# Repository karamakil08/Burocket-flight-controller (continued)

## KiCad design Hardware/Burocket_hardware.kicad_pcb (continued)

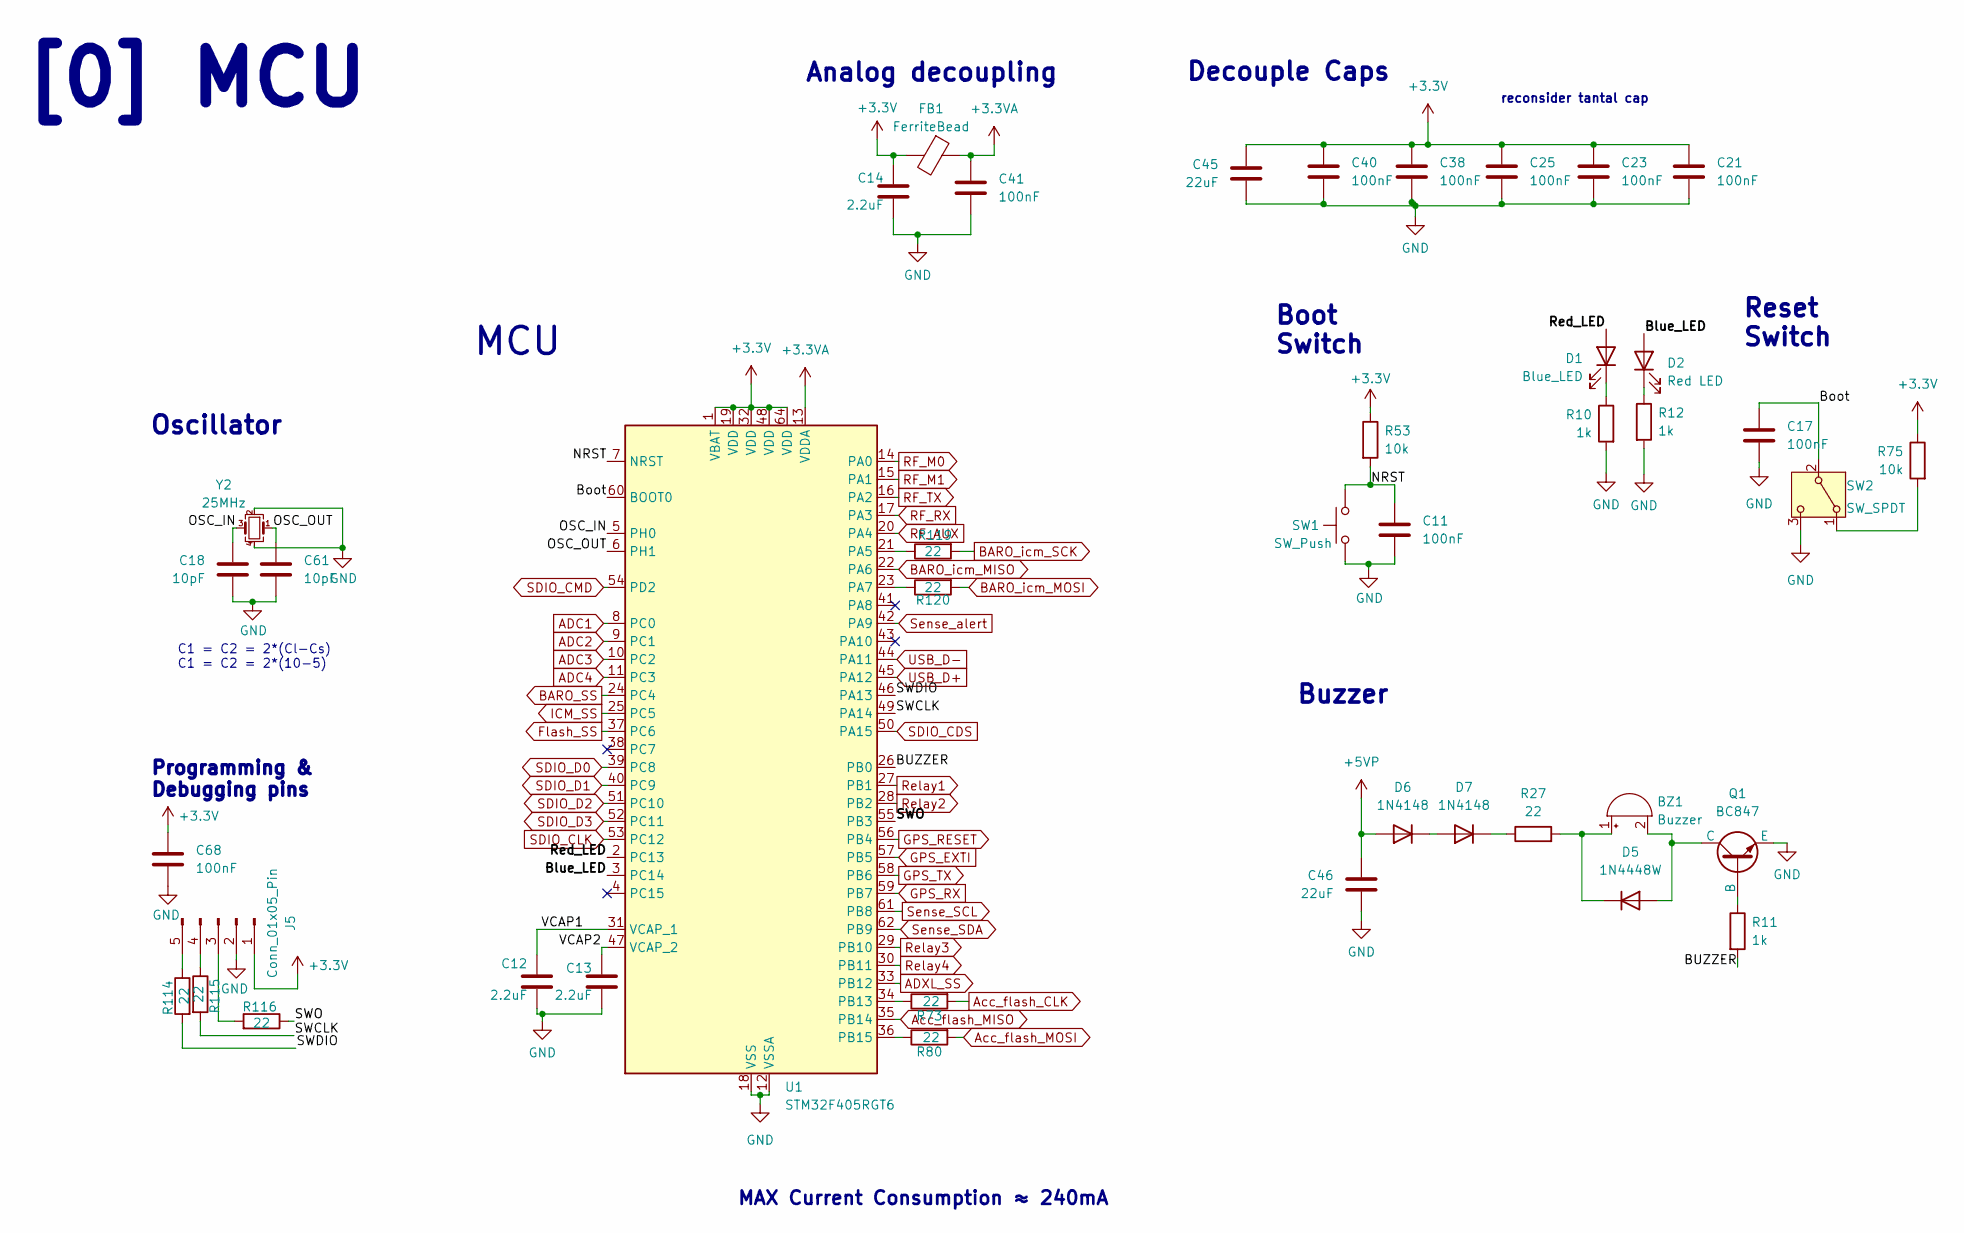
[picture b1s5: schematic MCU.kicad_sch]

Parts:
BZ1: Buzzer; Buzzer_typeshit; Part Number L-KLS3-SMT-3020-3V
C11, C17, C21, C23, C25, C38, C40, C41, C68: 100nF; C_0603_1608Metric; Part Number CL10B104KO8WPNC
C12, C13, C14: 2.2uF; C_0603_1608Metric; Part Number CL10B225KP8NNNC
C18, C61: 10pF; C_0603_1608Metric; Part Number CL10C100JB81PNC
C45, C46: 22uF; C_0805_2012Metric; Part Number CL21A226KOQNNNE
D1: Blue_LED; C_0603_1608Metric; Part Number HL-PST-1608H203BC
D2: Red LED; C_0603_1608Metric; Part Number 27-21/R6C-AP1Q2B/3C
D5: 1N4448W; Nexperia_CFP3_SOD-123W; Part Number 1N4448W_R1_00001
D6, D7: 1N4148; D_SOD-523; Part Number 1N4148WT
FB1: FerriteBead; R_0603_1608Metric; Part Number BLM18HE601SN1D
J5: Conn_01x05_Pin; PinHeader_1x05_P2.54mm_Vertical
Q1: BC847; SOT-323_SC-70; Part Number BC817-40W_R1_00001
R10, R11, R12: 1k; R_0603_1608Metric; Part Number CRCW06031K00JNTABC
R27: 22; R_0603_1608Metric; Part Number ERJPA3J220V
R53, R75: 10k; R_0603_1608Metric; Part Number CRT03J7E1002
R73, R80, R114, R115, R116, R119, R120: 22; R_0603_1608Metric; Part Number CQ03SAJ0220T5E
SW1: SW_Push; SW_SPST_PTS810; Part Number PTS815SJK250SMTRLFS
SW2: SW_SPDT; SW_SPDT_CK_JS102011SAQN; Part Number L-KLS7-MSK-12C03
U1: STM32F405RGT6; LQFP-64_10x10mm_P0.5mm
Y2: 25MHz; Crystal_SMD_2520-4Pin_2.5x2.0mm; Part Number ECS-250-10-36Q-ES-TR

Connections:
+3.3V: C14.1, C21.1, C23.1, C25.1, C38.1, C40.1, C45.1, C68.1, FB1.2, J5.1, R53.1, R75.1, U1.1 (VBAT), U1.19 (VDD), U1.32 (VDD), U1.48 (VDD), U1.64 (VDD); also elsewhere on the board
+3.3VA: C41.1, FB1.1, U1.13 (VDDA)
+5VP: C46.1, D6.2 (A); also elsewhere on the board
/MCU/BUZZER: R11.2, U1.26 (PB0)
/MCU/Blue_LED: D2.2 (A), U1.3 (PC14)
/MCU/Boot: C17.1, SW2.2 (B), U1.60 (BOOT0)
/MCU/NRST: C11.1, R53.2, SW1.2, U1.7 (NRST)
/MCU/OSC_IN: C18.1, U1.5 (PH0), Y2.3
/MCU/OSC_OUT: C61.1, U1.6 (PH1), Y2.1
/MCU/Red_LED: D1.2 (A), U1.2 (PC13)
/MCU/SWCLK: R115.2, U1.49 (PA14)
/MCU/SWDIO: R114.2, U1.46 (PA13)
/MCU/SWO: R116.1, U1.55 (PB3)
/MCU/VCAP1: C12.1, U1.31 (VCAP_1)
/MCU/VCAP2: C13.1, U1.47 (VCAP_2)
ADC1: U1.8 (PC0); also elsewhere on the board
ADC2: U1.9 (PC1); also elsewhere on the board
ADC3: U1.10 (PC2); also elsewhere on the board
ADC4: U1.11 (PC3); also elsewhere on the board
ADXL_SS: U1.33 (PB12); also elsewhere on the board
Acc_flash_CLK: R73.2; also elsewhere on the board
Acc_flash_MOSI: R80.2; also elsewhere on the board
BARO_SS: U1.24 (PC4); also elsewhere on the board
BARO_icm_MOSI: R120.2; also elsewhere on the board
Flash_SS: U1.37 (PC6); also elsewhere on the board
GND: C11.2, C12.2, C13.2, C14.2, C17.2, C18.2, C21.2, C23.2, C25.2, C38.2, C40.2, C41.2, C45.2, C46.2, C61.2, C68.2, J5.2, Q1.3 (E), R10.2, R12.2, SW1.1, SW2.3 (C), U1.12 (VSSA), U1.18 (VSS), U1.63 (VSS), Y2.2, Y2.4; also elsewhere on the board
GPS_EXTI: U1.57 (PB5); also elsewhere on the board
GPS_RESET: U1.56 (PB4); also elsewhere on the board
GPS_RX: U1.59 (PB7); also elsewhere on the board
GPS_TX: U1.58 (PB6); also elsewhere on the board
unnamed: BZ1.1 (+), D5.1 (K), R27.2
unnamed: BZ1.2 (-), D5.2 (A), Q1.1 (C)
unnamed: D1.1 (K), R10.1
unnamed: D2.1 (K), R12.1
unnamed: D6.1 (K), D7.2 (A)
unnamed: D7.1 (K), R27.1
unnamed: J5.3, R116.2
unnamed: J5.4, R115.1
unnamed: J5.5, R114.1
unnamed: Q1.2 (B), R11.1
unnamed: R75.2, SW2.1 (A)
unnamed: R119.1, U1.21 (PA5)
unnamed: R120.1, U1.23 (PA7)
unnamed: R73.1, U1.34 (PB13)
unnamed: R80.1, U1.36 (PB15)
RF_AUX: U1.20 (PA4); also elsewhere on the board
RF_M0: U1.14 (PA0); also elsewhere on the board
RF_M1: U1.15 (PA1); also elsewhere on the board
RF_RX: U1.17 (PA3); also elsewhere on the board
RF_TX: U1.16 (PA2); also elsewhere on the board
Relay1: U1.27 (PB1); also elsewhere on the board
Relay2: U1.28 (PB2); also elsewhere on the board
Relay3: U1.29 (PB10); also elsewhere on the board
Relay4: U1.30 (PB11); also elsewhere on the board
SDIO_CDS: U1.50 (PA15); also elsewhere on the board
SDIO_CLK: U1.53 (PC12); also elsewhere on the board
SDIO_CMD: U1.54 (PD2); also elsewhere on the board
SDIO_D0: U1.39 (PC8); also elsewhere on the board
SDIO_D1: U1.40 (PC9); also elsewhere on the board
SDIO_D2: U1.51 (PC10); also elsewhere on the board
SDIO_D3: U1.52 (PC11); also elsewhere on the board
Sense_SCL: U1.61 (PB8); also elsewhere on the board
Sense_SDA: U1.62 (PB9); also elsewhere on the board
Sense_alert: U1.42 (PA9); also elsewhere on the board
USB_D+: U1.45 (PA12); also elsewhere on the board
USB_D-: U1.44 (PA11); also elsewhere on the board

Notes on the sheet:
MCU
Reset Switch
Oscillator
Programming & Debugging pins
Decouple Caps
MAX Current Consumption ≈ 240mA
C1 = C2 = 2*(Cl-Cs) C1 = C2 = 2*(10-5)
Analog decoupling
Buzzer
Boot Switch
reconsider tantal cap
[0] MCU

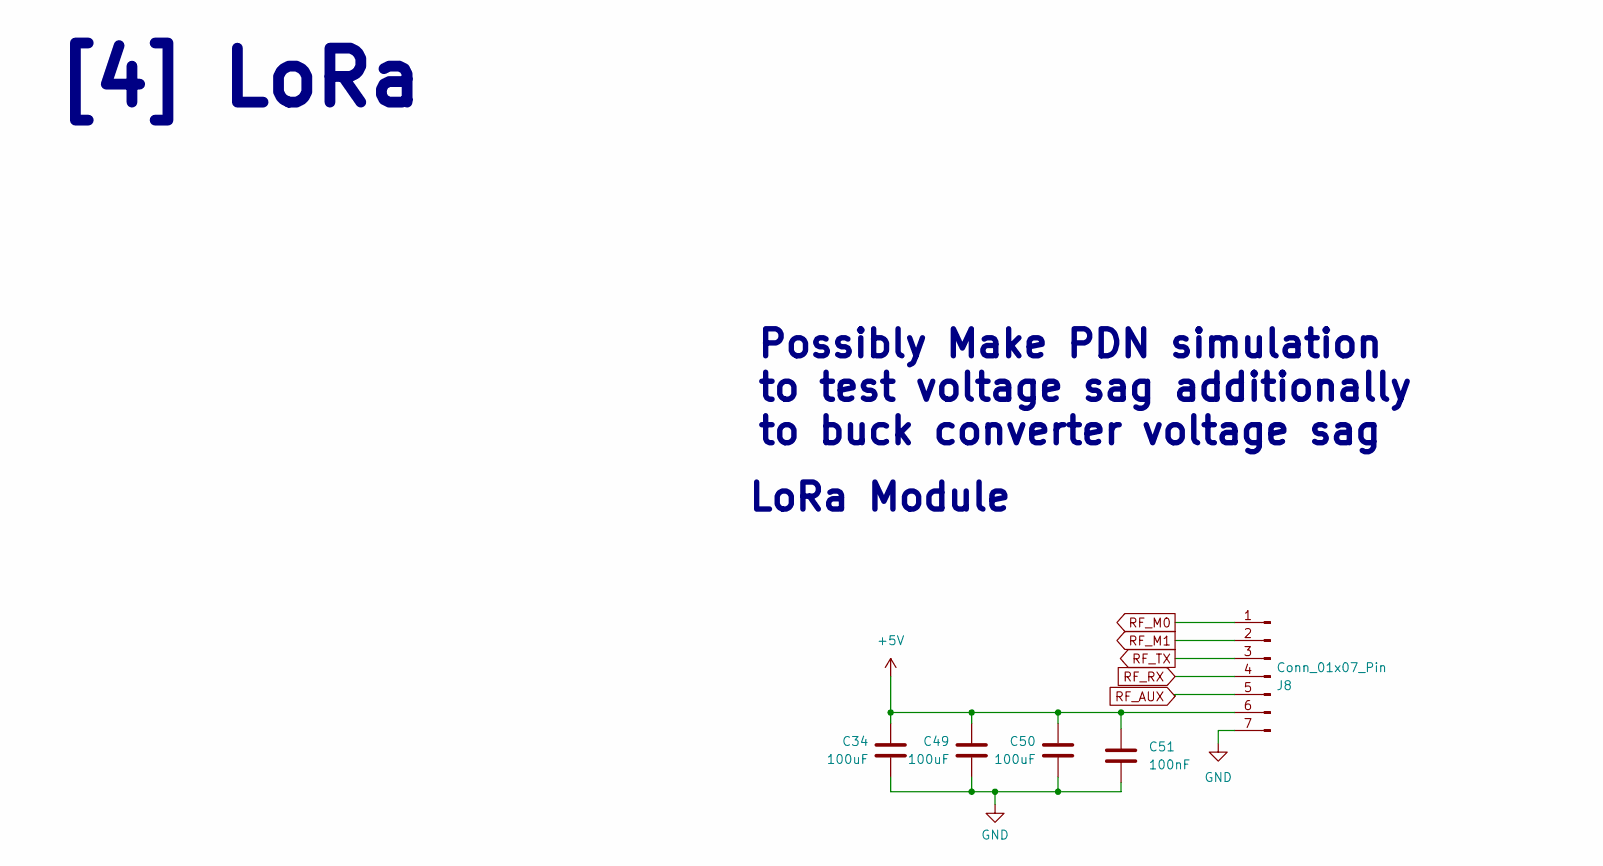
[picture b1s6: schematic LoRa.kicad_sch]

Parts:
C34, C49, C50: 100uF; CP_EIA-6032-20_AVX-F; Part Number 293D107X0010C2TE3
C51: 100nF; C_0603_1608Metric; Part Number CL10B104KO8WPNC
J8: Conn_01x07_Pin; E32-900T30D

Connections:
+5V: C34.1, C49.1, C50.1, C51.1, J8.6; also elsewhere on the board
GND: C34.2, C49.2, C50.2, C51.2, J8.7; also elsewhere on the board
unnamed 61: J8.3; also elsewhere on the board
unnamed 62: J8.4; also elsewhere on the board
unnamed 63: J8.5; also elsewhere on the board
RF_M0: J8.1; also elsewhere on the board
RF_M1: J8.2; also elsewhere on the board

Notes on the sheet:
Possibly Make PDN simulation to test voltage sag additionally to buck converter voltage sag
LoRa Module
[4] LoRa

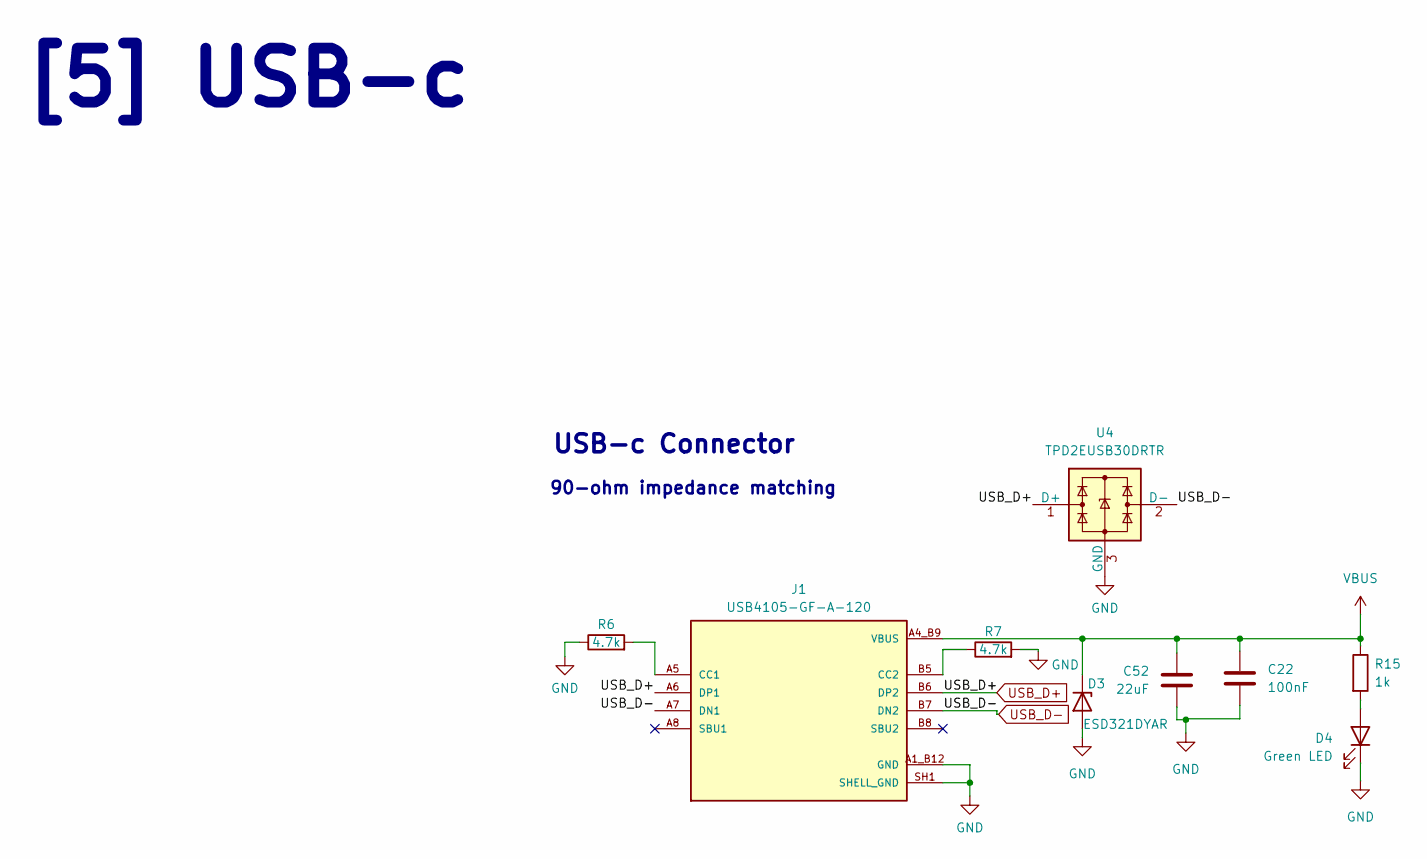
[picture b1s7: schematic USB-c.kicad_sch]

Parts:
C22: 100nF; C_0603_1608Metric; Part Number CL10B104KO8WPNC
C52: 22uF; C_0805_2012Metric; Part Number CL21A226KOQNNNE
D3: ESD321DYAR; D_SOD-523; Part Number ESD321DYAR
D4: Green LED; LED_0603_1608Metric; Part Number HL-PST-1608U51GC
J1: USB4105-GF-A-120; GCT_USB4105-GF-A-120; Part Number USB4105-GF-A-120
R6, R7: 4.7k; R_0603_1608Metric; Part Number CQ03SAJ0472T5E
R15: 1k; R_0603_1608Metric; Part Number CRCW06031K00JNTABC
U4: TPD2EUSB30DRTR; Texas_DRT-3; Part Number TPD2EUSB30DRTR

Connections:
GND: C22.2, C52.2, D3.2 (A), D4.1 (K), J1.A1_B12 (GND), J1.B1_A12 (GND), J1.SH1 (SHELL_GND), J1.SH2 (SHELL_GND), J1.SH3 (SHELL_GND), J1.SH4 (SHELL_GND), R6.1, R7.2, U4.3 (GND); also elsewhere on the board
unnamed: D4.2 (A), R15.2
unnamed 49: J1.A5 (CC1), R6.2; also elsewhere on the board
unnamed: J1.B5 (CC2), R7.1
USB_D+: J1.A6 (DP1), J1.B6 (DP2), U4.1 (D+); also elsewhere on the board
USB_D-: J1.A7 (DN1), J1.B7 (DN2), U4.2 (D-); also elsewhere on the board
VBUS: C22.1, C52.1, D3.1 (K), J1.A4_B9 (VBUS), J1.B4_A9 (VBUS), R15.1; also elsewhere on the board

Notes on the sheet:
USB-c Connector
[5] USB-c
90-ohm impedance matching

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
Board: 4 copper layers, 195 parts (54 on the bottom side), 129 nets, no tracks yet.

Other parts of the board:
C24: 2.2uF; C_0603_1608Metric
C63, C67: 100nF; C_0603_1608Metric
J2: Conn_Coaxial; SMA_Amphenol_132134-10_Vertical
R8: 5.1k; R_0603_1608Metric
R9, R14, R16: 220; R_0603_1608Metric
R17, R18: 4.7k; R_0603_1608Metric
R108, R118, R121, R122: 22; R_0603_1608Metric
TP1: TestPoint; Burocket Logo

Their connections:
+3.3V: C24.1, C63.1, C67.1, R17.2, R18.2; also elsewhere on the board
/Sensors/Connector_feed: J2.1 (In); also elsewhere on the board
ADXL_SS: R118.2; also elsewhere on the board
BARO_SS: R121.2; also elsewhere on the board
GND: C24.2, C63.2, C67.2, J2.2 (Ext), R8.1; also elsewhere on the board
GPS_EXTI: R16.1; also elsewhere on the board
GPS_RESET: R14.1; also elsewhere on the board
unnamed 49: R8.2; also elsewhere on the board
unnamed 61: R122.1; also elsewhere on the board
unnamed 62: R108.1; also elsewhere on the board
unnamed 63: R9.2; also elsewhere on the board
unnamed 78: R121.1; also elsewhere on the board
unnamed 86: R118.1; also elsewhere on the board
unnamed 93: R16.2; also elsewhere on the board
unnamed 94: R14.2; also elsewhere on the board
RF_AUX: R9.1; also elsewhere on the board
RF_M0: R17.1; also elsewhere on the board
RF_M1: R18.1; also elsewhere on the board
RF_RX: R108.2; also elsewhere on the board
RF_TX: R122.2; also elsewhere on the board

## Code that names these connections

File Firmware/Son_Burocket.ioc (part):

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Mcu.Name=STM32F405RGTx
Mcu.Package=LQFP64
Mcu.UserName=STM32F405RGTx
PA0-WKUP.GPIOParameters=GPIO_Label
PA0-WKUP.GPIO_Label=RF_M0
PA0-WKUP.Signal=GPIO_Output
PA1.GPIOParameters=GPIO_Label
PA1.GPIO_Label=RF_M1
PA1.Signal=GPIO_Output
PA11.Mode=Device_Only
PA11.Signal=USB_OTG_FS_DM
PA12.Mode=Device_Only
PA12.Signal=USB_OTG_FS_DP
PA13.Mode=Trace_Asynchronous_SW
PA13.Signal=SYS_JTMS-SWDIO
PA14.Mode=Trace_Asynchronous_SW
PA14.Signal=SYS_JTCK-SWCLK
PA15.GPIOParameters=GPIO_Label
PA15.GPIO_Label=SDIO_CDS
PA15.Signal=GPIO_Input
PA2.GPIOParameters=GPIO_Label
PA2.GPIO_Label=RF_TX
PA2.Mode=Asynchronous
PA2.Signal=USART2_TX
PA3.GPIOParameters=GPIO_Label
PA3.GPIO_Label=RF_RX
PA3.Mode=Asynchronous
PA3.Signal=USART2_RX
PA4.GPIOParameters=GPIO_Label
PA4.GPIO_Label=RF_AUX
PA4.Signal=GPXTI4
PA5.GPIOParameters=GPIO_Label
PA5.GPIO_Label=Baro_icm_SCK
PA5.Mode=Full_Duplex_Master
PA5.Signal=SPI1_SCK
PA6.GPIOParameters=GPIO_Label
PA6.GPIO_Label=BARO_icm_MISO
PA6.Mode=Full_Duplex_Master
PA6.Signal=SPI1_MISO
PA7.GPIOParameters=GPIO_Label
PA7.GPIO_Label=Baro_icm_MOSI
PA7.Mode=Full_Duplex_Master
PA7.Signal=SPI1_MOSI
PA9.GPIOParameters=GPIO_Label,GPIO_ModeDefaultEXTI
PA9.GPIO_Label=Sense_alert
PA9.GPIO_ModeDefaultEXTI=GPIO_MODE_IT_FALLING
PA9.Signal=GPXTI9
PB0.GPIOParameters=GPIO_Label
PB0.GPIO_Label=Buzzer
PB0.Signal=S_TIM3_CH3
PB1.GPIOParameters=GPIO_Label
PB1.GPIO_Label=Relay1
PB1.Signal=GPIO_Output
PB10.GPIOParameters=GPIO_Label
PB10.GPIO_Label=Relay3
PB10.Signal=GPIO_Output
PB11.GPIOParameters=GPIO_Label
PB11.GPIO_Label=Relay4
PB11.Signal=GPIO_Output
PB12.GPIOParameters=GPIO_Label
PB12.GPIO_Label=ADXL_SS
PB12.Signal=GPIO_Output
PB13.GPIOParameters=GPIO_Label
PB13.GPIO_Label=Acc_flash_SCK
PB13.Mode=Full_Duplex_Master
PB13.Signal=SPI2_SCK
PB14.GPIOParameters=GPIO_Label
PB14.GPIO_Label=Acc_flash_MISO
PB14.Mode=Full_Duplex_Master
PB14.Signal=SPI2_MISO
PB15.GPIOParameters=GPIO_Label
PB15.GPIO_Label=Acc_flash_MOSI
PB15.Mode=Full_Duplex_Master
PB15.Signal=SPI2_MOSI
PB2.GPIOParameters=GPIO_Label
PB2.GPIO_Label=Relay2
PB2.Signal=GPIO_Output
PB3.Mode=Trace_Asynchronous_SW
PB3.Signal=SYS_JTDO-SWO
PB4.GPIOParameters=GPIO_Label
PB4.GPIO_Label=GPS_RESET
PB4.Signal=GPIO_Output
PB5.GPIOParameters=GPIO_Label
PB5.GPIO_Label=GPS_EXTI
PB5.Signal=GPIO_Input
PB6.GPIOParameters=GPIO_Label
PB6.GPIO_Label=GPS_TX
PB6.Mode=Asynchronous
PB6.Signal=USART1_TX
PB7.GPIOParameters=GPIO_Label
PB7.GPIO_Label=GPS_RX
PB7.Mode=Asynchronous
PB7.Signal=USART1_RX
PB8.GPIOParameters=GPIO_Label
PB8.GPIO_Label=Sense_SCL
PB8.Mode=I2C
PB8.Signal=I2C1_SCL
PB9.GPIOParameters=GPIO_Label
PB9.GPIO_Label=Sense_SDA
PB9.Mode=I2C
PB9.Signal=I2C1_SDA
PC0.GPIOParameters=GPIO_Label
PC0.GPIO_Label=ADC1
PC0.Signal=ADCx_IN10
PC1.GPIOParameters=GPIO_Label
PC1.GPIO_Label=ADC2
PC1.Signal=ADCx_IN11
PC10.Mode=SD_4_bits_Wide_bus
PC10.Signal=SDIO_D2
PC11.Mode=SD_4_bits_Wide_bus
PC11.Signal=SDIO_D3
PC12.Mode=SD_4_bits_Wide_bus
PC12.Signal=SDIO_CK
PC13-ANTI_TAMP.GPIOParameters=GPIO_Label
PC13-ANTI_TAMP.GPIO_Label=Red_LED
PC13-ANTI_TAMP.Signal=GPIO_Output
PC14-OSC32_IN.GPIOParameters=GPIO_Label
PC14-OSC32_IN.GPIO_Label=Blue_LED
PC14-OSC32_IN.Signal=GPIO_Output
PC2.GPIOParameters=GPIO_Label
PC2.GPIO_Label=ADC3
PC2.Signal=ADCx_IN12
PC3.GPIOParameters=GPIO_Label
PC3.GPIO_Label=ADC4
PC3.Signal=ADCx_IN13
PC4.GPIOParameters=GPIO_Label
PC4.GPIO_Label=Baro_SS
PC4.Signal=GPIO_Output
PC5.GPIOParameters=GPIO_Label
PC5.GPIO_Label=ICM_SS
PC5.Signal=GPIO_Output
PC6.GPIOParameters=GPIO_Label
PC6.GPIO_Label=Flash_SS
PC6.Signal=GPIO_Output
PC8.Mode=SD_4_bits_Wide_bus
PC8.Signal=SDIO_D0
PC9.Mode=SD_4_bits_Wide_bus
PC9.Signal=SDIO_D1
PD2.Mode=SD_4_bits_Wide_bus
PD2.Signal=SDIO_CMD
PH0-OSC_IN.Mode=HSE-External-Clock-Source
PH0-OSC_IN.Signal=RCC_OSC_IN
PH1-OSC_OUT.Mode=HSE-External-Clock-Source
PH1-OSC_OUT.Signal=RCC_OSC_OUT
RCC.HSE_VALUE=25000000
RCC.SYSCLKFreq_VALUE=168000000
RCC.SYSCLKSource=RCC_SYSCLKSOURCE_PLLCLK
board=custom
